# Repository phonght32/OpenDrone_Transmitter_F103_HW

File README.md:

# OpenDrone_Transmitter_F103_HW

Version 2.0

### Overview

OpenDrone Project - Transmitter hardware using STM32F103.

### Specifications

### Layout/Pin map

### Design

#### Schematic

#### PCB

F.Cu

B.Cu

#### 3D top

#### 3D bottom

#### Dimension

### Bill of materials (BOM)

[Download v1.0](Assets/BOM/OpenDrone_Transmitter_F103_HW_v1.0.xlsx)

[Download v2.0](Assets/BOM/OpenDrone_Transmitter_F103_HW_v2.0.xlsx)

### Gerber

[Download v1.0](Assets/Gerber/Gerber_OpenDrone_Transmitter_F103_HW_v1.0.zip)

[Download v2.0](Assets/Gerber/Gerber_OpenDrone_Transmitter_F103_HW_v2.0.zip)

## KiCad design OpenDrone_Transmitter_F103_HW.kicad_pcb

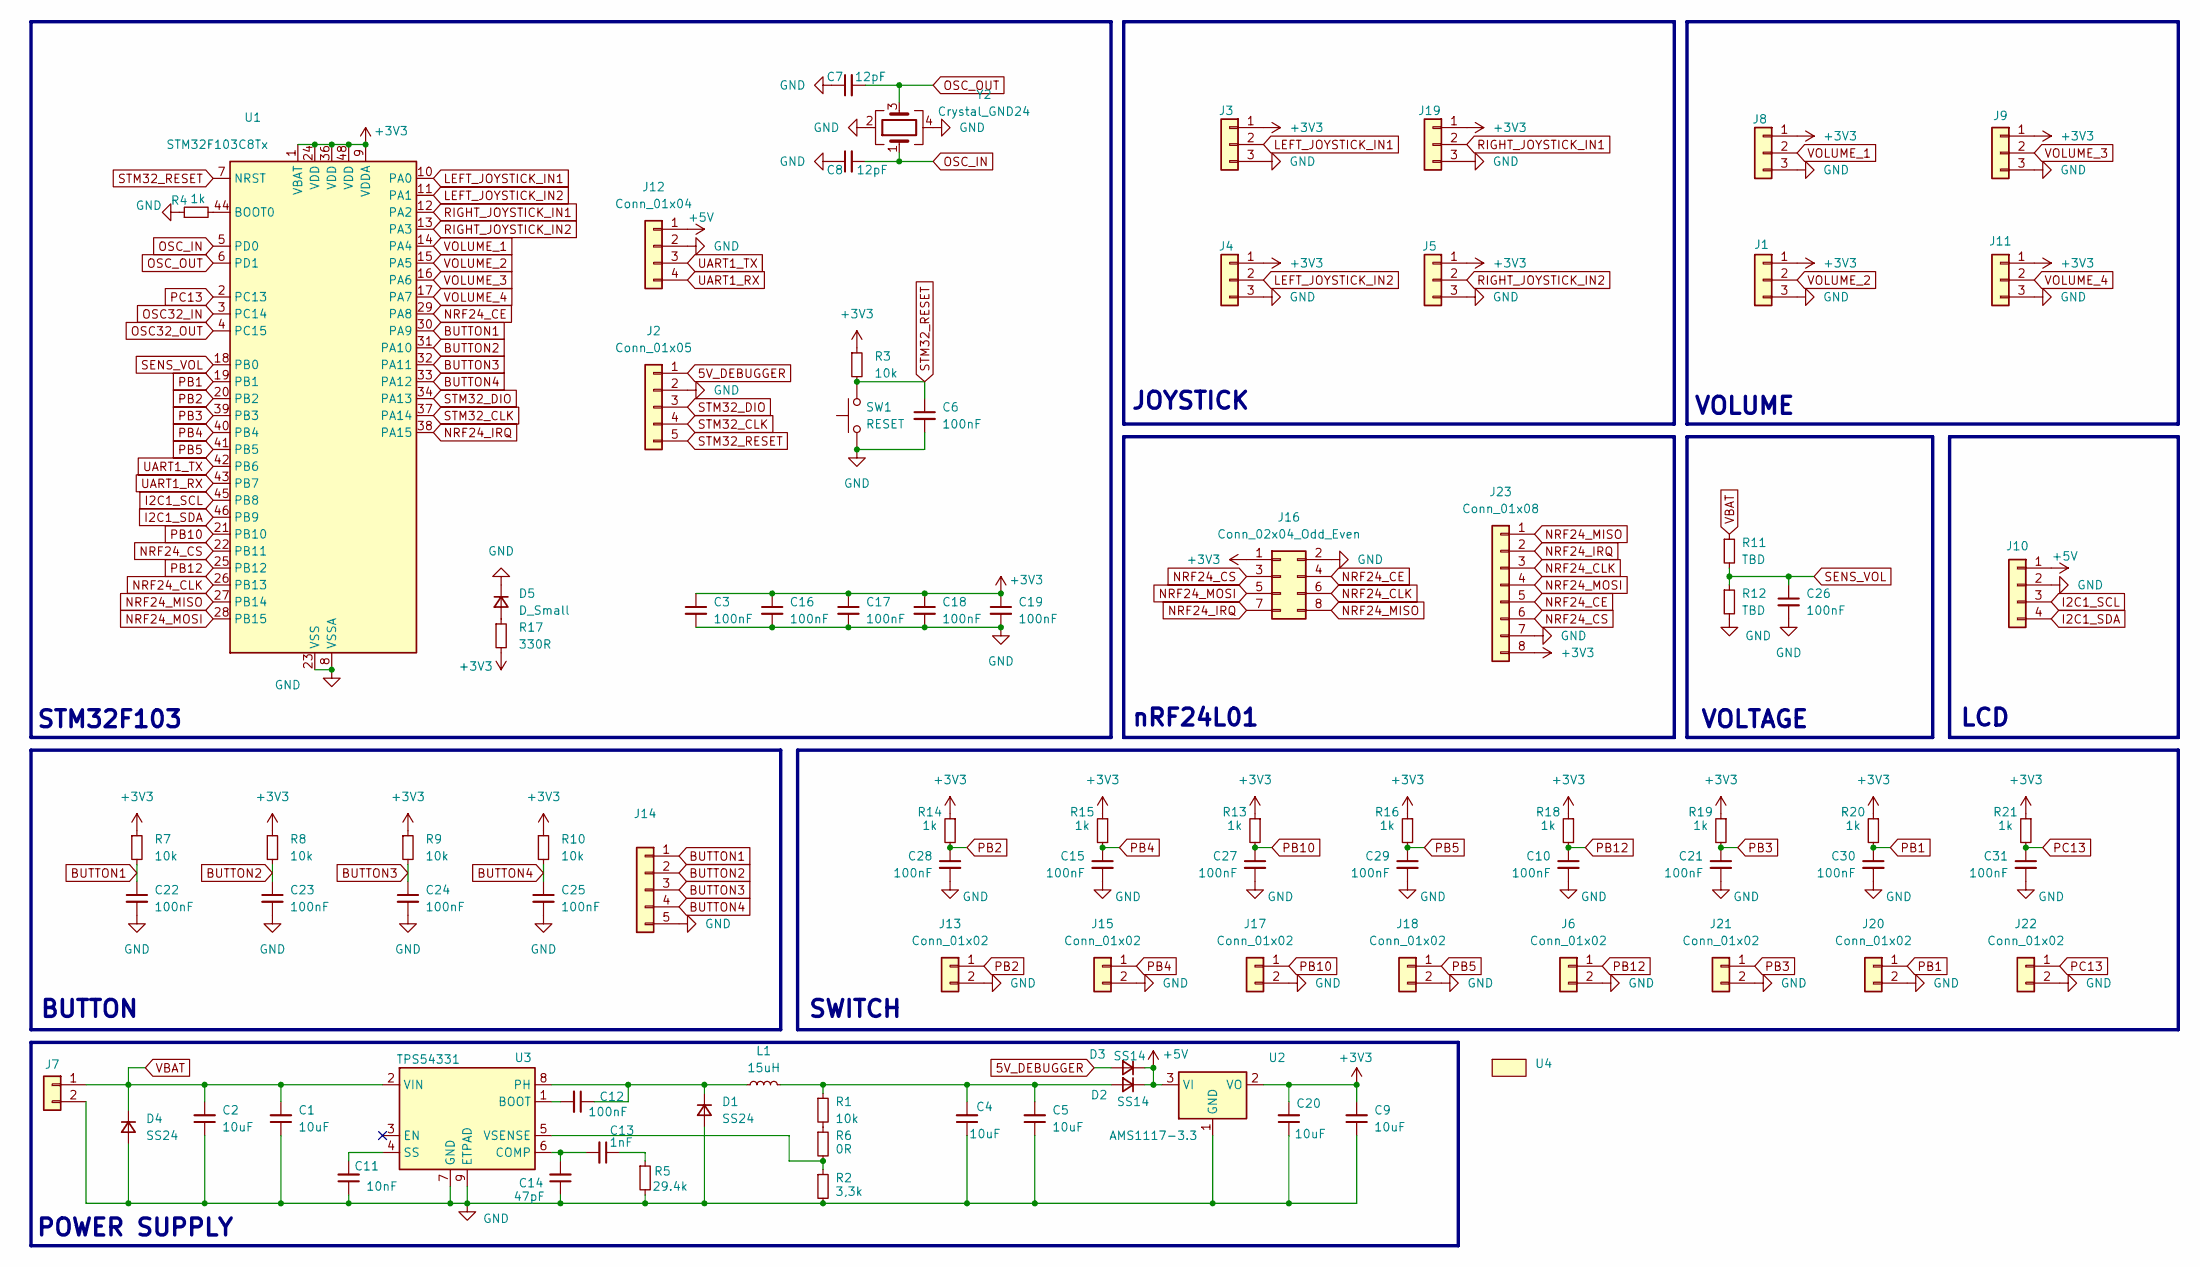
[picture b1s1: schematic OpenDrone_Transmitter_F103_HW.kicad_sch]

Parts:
C1, C2, C4, C5, C9, C20: 10uF; C_1210_3225Metric
C3, C6, C10, C12, C15, C16, C17, C18, C19, C21, C22, C23, C24, C25, C26, C27, C28, C29, C30, C31: 100nF; C_0603_1608Metric
C7, C8: 12pF; C_0603_1608Metric
C11: 10nF; C_0603_1608Metric
C13: 1nF; C_0603_1608Metric
C14: 47pF; C_0603_1608Metric
D1, D4: SS24; D_SMA
D2, D3: SS14; D_SMA
D5: D_Small; LED_0603_1608Metric
J1, J3, J4, J5, J8, J9, J11, J19: Conn_01x03; Connector_ZH_1x03_P1.25mm_Vertical
J2, J14: Conn_01x05; Connector_ZH_1x05_P1.25mm_Vertical
J6, J7, J13, J15, J17, J18, J20, J21, J22: Conn_01x02; Connector_ZH_1x02_P1.25mm_Vertical
J10, J12: Conn_01x04; Connector_ZH_1x04_P1.25mm_Vertical
J16: Conn_02x04_Odd_Even; PinSocket_2x04_P2.54mm_Vertical
J23: Conn_01x08; Connector_ZH_1x08_P1.25mm_Vertical
L1: 15uH; Inductor_SMD_4D28
R1, R3, R7, R8, R9, R10: 10k; R_0603_1608Metric
R2: 3,3k; R_0603_1608Metric
R4, R13, R14, R15, R16, R18, R19, R20, R21: 1k; R_0603_1608Metric
R5: 29.4k; R_0603_1608Metric
R6: 0R; R_0603_1608Metric
R11, R12: TBD; R_0603_1608Metric
R17: 330R; R_0603_1608Metric
SW1: RESET; Button_SMD_4.2x3.3x2.5mm
U1: STM32F103C8Tx; LQFP-48_7x7mm_P0.5mm
U2: AMS1117-3.3; SOT-223-3_TabPin2
U3: TPS54331; SOIC-8-1EP_3.9x4.9mm_P1.27mm_EP2.29x3mm
U4: Board
Y2: Crystal_GND24; Crystal_SMD_3225-4Pin_3.2x2.5mm

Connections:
5V_DEBUGGER: D3.2 (A), J2.1
+3V3: C3.1, C9.2, C16.1, C17.1, C18.1, C19.1, C20.2, J1.1, J3.1, J4.1, J5.1, J8.1, J9.1, J11.1, J16.1, J19.1, J23.8, R3.1, R7.1, R8.1, R9.1, R10.1, R13.1, R14.1, R15.1, R16.1, R17.2, R18.1, R19.1, R20.1, R21.1, U1.1 (VBAT), U1.9 (VDDA), U1.24 (VDD), U1.36 (VDD), U1.48 (VDD), U2.2 (VO)
+5V: D2.1 (K), D3.1 (K), J10.1, J12.1, U2.3 (VI)
BUTTON1: C22.1, J14.1, R7.2, U1.30 (PA9)
BUTTON2: C23.1, J14.2, R8.2, U1.31 (PA10)
BUTTON3: C24.1, J14.3, R9.2, U1.32 (PA11)
BUTTON4: C25.1, J14.4, R10.2, U1.33 (PA12)
GND: C1.1, C2.1, C3.2, C4.1, C5.1, C6.2, C7.1, C8.1, C9.1, C10.2, C11.1, C14.1, C15.2, C16.2, C17.2, C18.2, C19.2, C20.1, C21.2, C22.2, C23.2, C24.2, C25.2, C26.2, C27.2, C28.2, C29.2, C30.2, C31.2, D1.2 (A), D4.2 (A), D5.1 (K), J1.3, J2.2, J3.3, J4.3, J5.3, J6.2, J7.2, J8.3, J9.3, J10.2, J11.3, J12.2, J13.2, J14.5, J15.2, J16.2, J17.2, J18.2, J19.3, J20.2, J21.2, J22.2, J23.7, R2.2, R4.1, R5.2, R12.2, SW1.1, U1.8 (VSSA), U1.23 (VSS), U1.35 (VSS), U1.47 (VSS), U2.1 (GND), U3.7 (GND), U3.9 (ETPAD), Y2.2, Y2.4
I2C1_SCL: J10.3, U1.45 (PB8)
I2C1_SDA: J10.4, U1.46 (PB9)
LEFT_JOYSTICK_IN1: J3.2, U1.10 (PA0)
LEFT_JOYSTICK_IN2: J4.2, U1.11 (PA1)
NRF24_CE: J16.4, J23.5, U1.29 (PA8)
NRF24_CLK: J16.6, J23.3, U1.26 (PB13)
NRF24_CS: J16.3, J23.6, U1.22 (PB11)
NRF24_IRQ: J16.7, J23.2, U1.38 (PA15)
NRF24_MISO: J16.8, J23.1, U1.27 (PB14)
NRF24_MOSI: J16.5, J23.4, U1.28 (PB15)
unnamed: C13.1, R5.1
unnamed: C12.1, D1.1 (K), L1.1, U3.8 (PH)
unnamed: C4.2, C5.2, D2.2 (A), L1.2, R1.1
unnamed: D5.2 (A), R17.1
unnamed: R1.2, R6.1
unnamed: R4.2, U1.44 (BOOT0)
unnamed: C12.2, U3.1 (BOOT)
unnamed: C13.2, C14.2, U3.6 (COMP)
unnamed: C11.2, U3.4 (SS)
unnamed: R2.1, R6.2, U3.5 (VSENSE)
OSC32_IN: U1.3 (PC14)
OSC32_OUT: U1.4 (PC15)
OSC_IN: C8.2, U1.5 (PD0), Y2.1
OSC_OUT: C7.2, U1.6 (PD1), Y2.3
PB1: C30.1, J20.1, R20.2, U1.19 (PB1)
PB2: C28.1, J13.1, R14.2, U1.20 (PB2)
PB3: C21.1, J21.1, R19.2, U1.39 (PB3)
PB4: C15.1, J15.1, R15.2, U1.40 (PB4)
PB5: C29.1, J18.1, R16.2, U1.41 (PB5)
PB10: C27.1, J17.1, R13.2, U1.21 (PB10)
PB12: C10.1, J6.1, R18.2, U1.25 (PB12)
PC13: C31.1, J22.1, R21.2, U1.2 (PC13)
RIGHT_JOYSTICK_IN1: J19.2, U1.12 (PA2)
RIGHT_JOYSTICK_IN2: J5.2, U1.13 (PA3)
SENS_VOL: C26.1, R11.2, R12.1, U1.18 (PB0)
STM32_CLK: J2.4, U1.37 (PA14)
STM32_DIO: J2.3, U1.34 (PA13)
STM32_RESET: C6.1, J2.5, R3.2, SW1.2, U1.7 (NRST)
UART1_RX: J12.4, U1.43 (PB7)
UART1_TX: J12.3, U1.42 (PB6)
VBAT: C1.2, C2.2, D4.1 (K), J7.1, R11.1, U3.2 (VIN)
VOLUME_1: J8.2, U1.14 (PA4)
VOLUME_2: J1.2, U1.15 (PA5)
VOLUME_3: J9.2, U1.16 (PA6)
VOLUME_4: J11.2, U1.17 (PA7)

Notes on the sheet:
STM32F103
BUTTON
POWER SUPPLY
JOYSTICK
SWITCH
VOLTAGE
nRF24L01
LCD
VOLUME

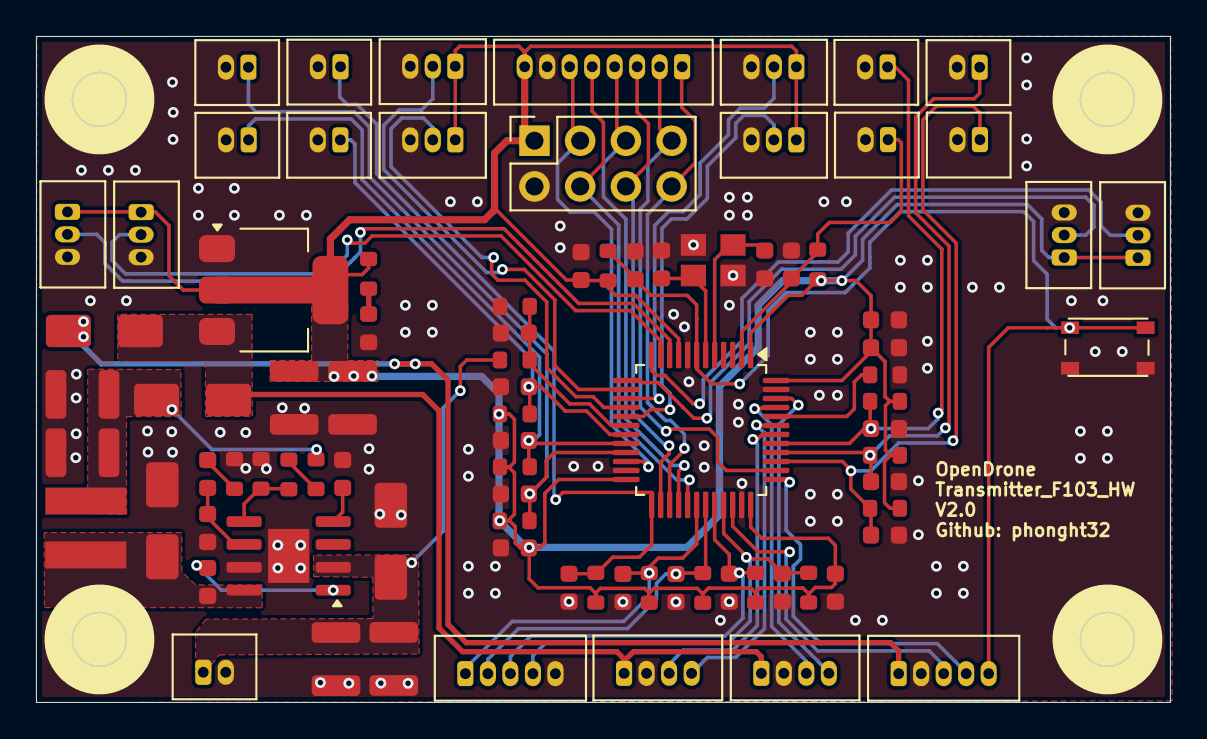
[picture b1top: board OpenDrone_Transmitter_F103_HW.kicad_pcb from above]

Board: 2 copper layers, 63.0 x 37.0 mm, 87 parts (0 on the bottom side), 51 nets.

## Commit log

2024-08-31 update project
2024-09-10 update assets
2024-09-10 complete v1.0
2024-12-14 update library
2024-12-15 update gitignore
2024-12-15 remove step file
2024-12-15 update PCB
2024-12-15 update text
2024-12-15 update dimension measurement
2024-12-15 update board size
2024-12-23 update demo
2024-12-23 update schematic
2024-12-23 add gerber
2024-12-23 add BOM
2024-12-23 add image demo
2024-12-23 add schematic
2024-12-23 change name
2024-12-23 add README v2.0
2025-09-19 change pin order in joystick
